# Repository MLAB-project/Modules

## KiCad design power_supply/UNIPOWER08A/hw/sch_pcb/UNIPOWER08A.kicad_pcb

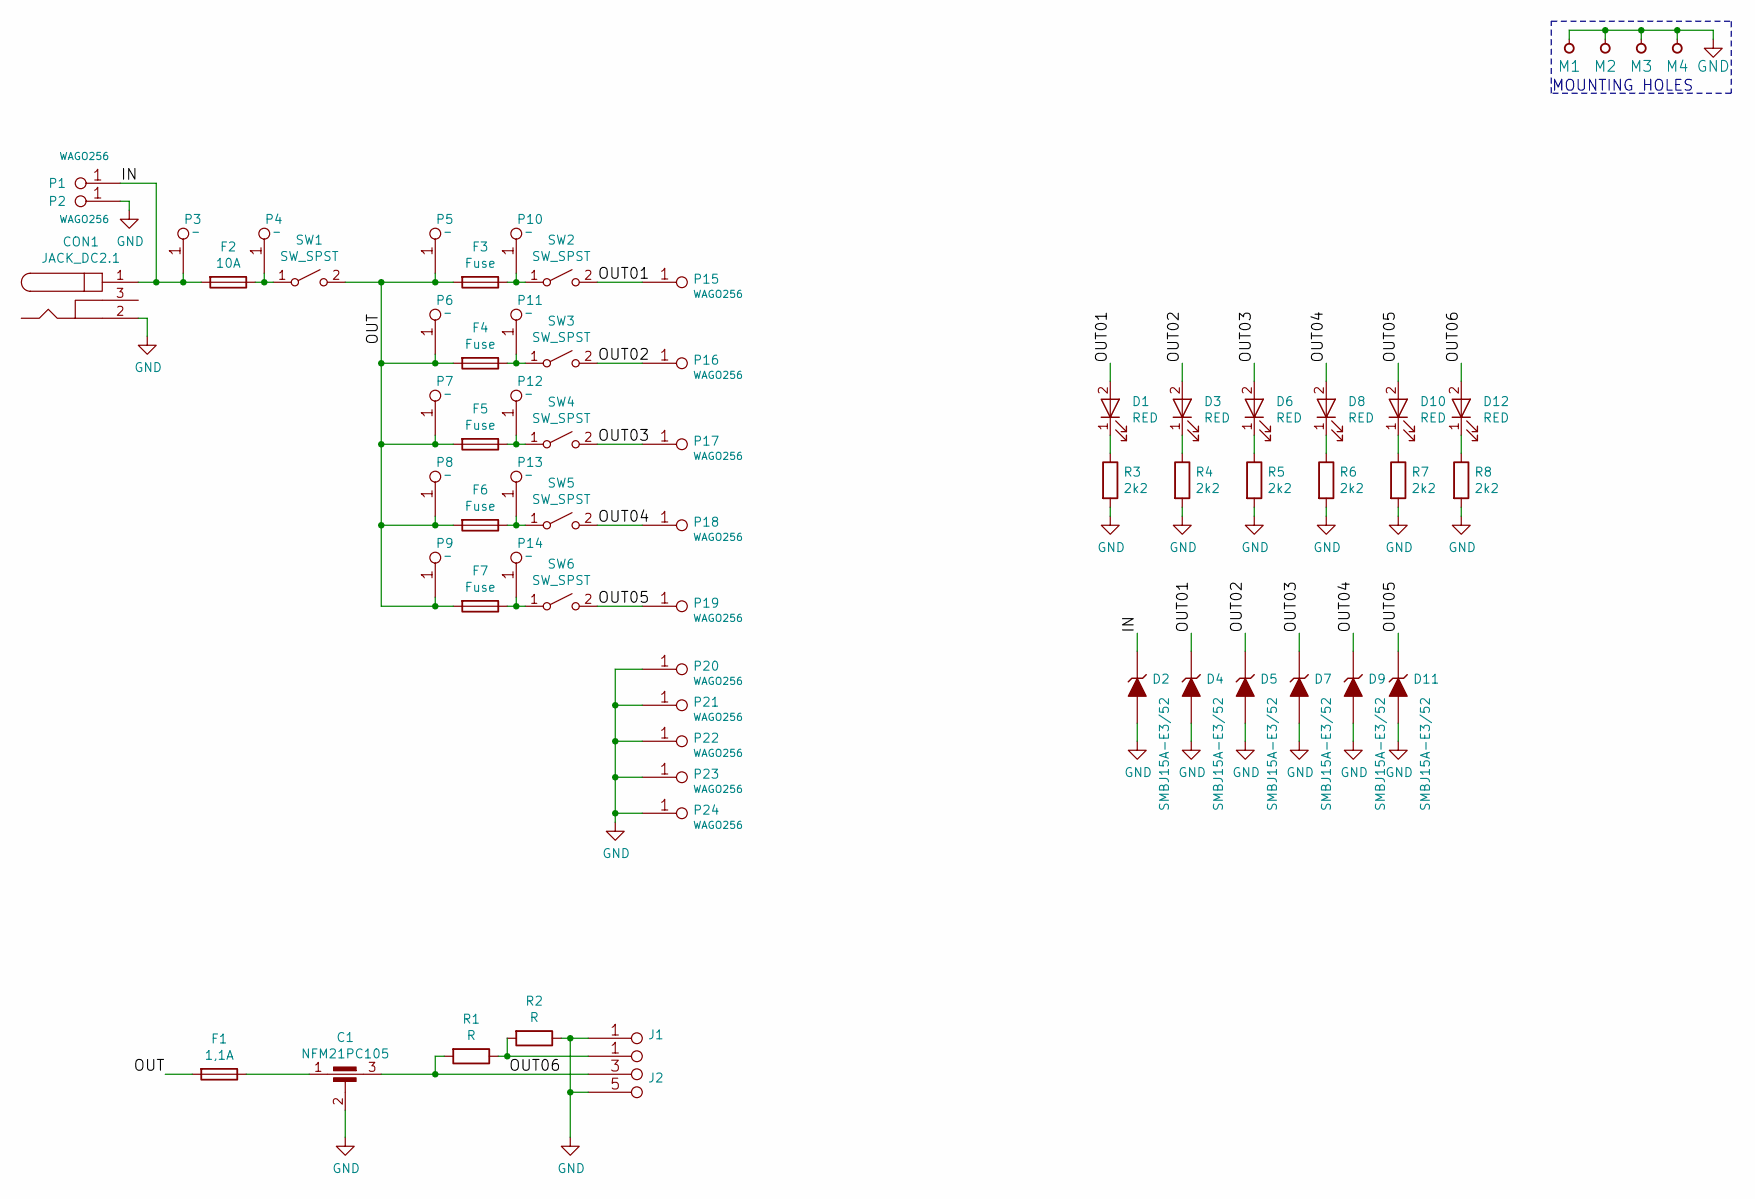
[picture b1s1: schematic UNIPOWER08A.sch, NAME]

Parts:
C1: NFM21PC105; FIR1
CON1: JACK_DC2.1; DC2,1MM
D1, D3, D6, D8, D10, D12: RED; LED_1206
D2, D4, D5, D7, D9, D11: SMBJ15A-E3/52; Diode-SMB_Standard
F1: 1,1A; Drzak_2410
F2: 10A; Drzak_2410
F3, F4, F5, F6, F7: Fuse; Drzak_2410
J1: JUMP_2x1; Straight_2x01
J2: JUMP_3X2; Straight_2x03
M1, M2, M3, M4: HOLE; MountingHole_3mm
P1, P2, P15, P16, P17, P18, P19, P20, P21, P22, P23, P24: WAGO256; WAGO256_2
P3, P4, P5, P6, P7, P8, P9, P10, P11, P12, P13, P14: _; 1_kontakty
R1, R2: R; SMD-0805
R3, R4, R5, R6, R7, R8: 2k2; SMD-0805
SW1, SW2, SW3, SW4, SW5, SW6: SW_SPST; 2_kontakty

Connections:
/IN: CON1.1, D2.1 (K), F2.2, P1.1, P3.1
/OUT: F1.2, F3.2, F4.2, F5.2, F6.2, F7.2, P5.1, P6.1, P7.1, P8.1, P9.1, SW1.2 (B)
/OUT01: D1.2 (A), D4.1 (K), P15.1, SW2.2 (B)
/OUT02: D3.2 (A), D5.1 (K), P16.1, SW3.2 (B)
/OUT03: D6.2 (A), D7.1 (K), P17.1, SW4.2 (B)
/OUT04: D8.2 (A), D9.1 (K), P18.1, SW5.2 (B)
/OUT05: D10.2 (A), D11.1 (K), P19.1, SW6.2 (B)
/OUT06: C1.3, D12.2 (A), J2.3 (4), J2.4, R1.2
GND: C1.2, CON1.2, D2.2 (A), D4.2 (A), D5.2 (A), D7.2 (A), D9.2 (A), D11.2 (A), J1.1, J1.2, J2.5 (6), J2.6, M1.1, M2.1, M3.1, M4.1, P2.1, P20.1, P21.1, P22.1, P23.1, P24.1, R2.1, R3.2, R4.2, R5.2, R6.2, R7.2, R8.2
unnamed: C1.1, F1.1
unnamed: D1.1 (K), R3.1
unnamed: D3.1 (K), R4.1
unnamed: D6.1 (K), R5.1
unnamed: D8.1 (K), R6.1
unnamed: D10.1 (K), R7.1
unnamed: D12.1 (K), R8.1
unnamed: F2.1, P4.1, SW1.1 (A)
unnamed: F3.1, P10.1, SW2.1 (A)
unnamed: F4.1, P11.1, SW3.1 (A)
unnamed: F5.1, P12.1, SW4.1 (A)
unnamed: F6.1, P13.1, SW5.1 (A)
unnamed: F7.1, P14.1, SW6.1 (A)
unnamed: J2.1 (2), J2.2, R1.1, R2.2

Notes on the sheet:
MOUNTING HOLES

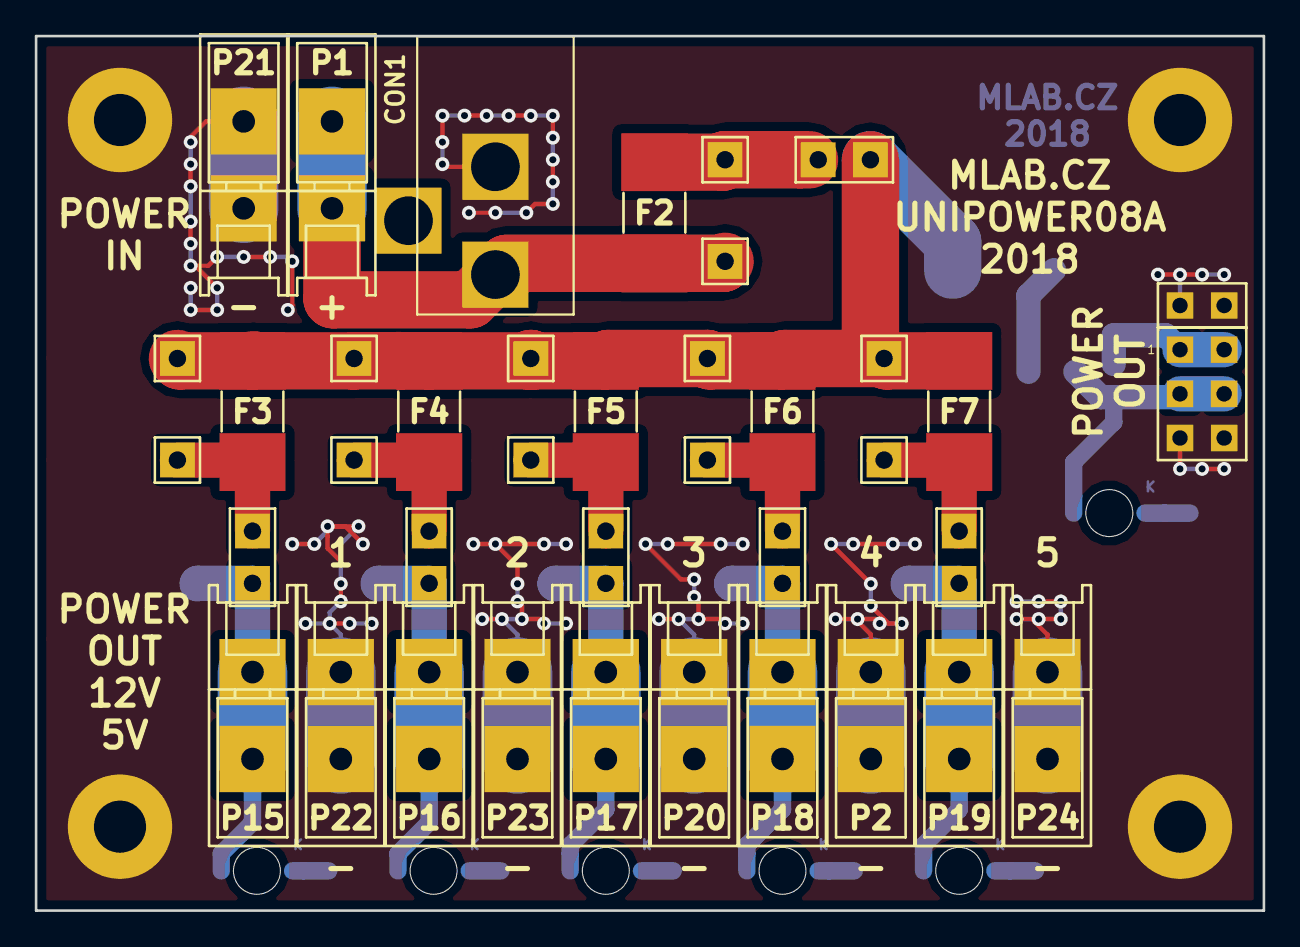
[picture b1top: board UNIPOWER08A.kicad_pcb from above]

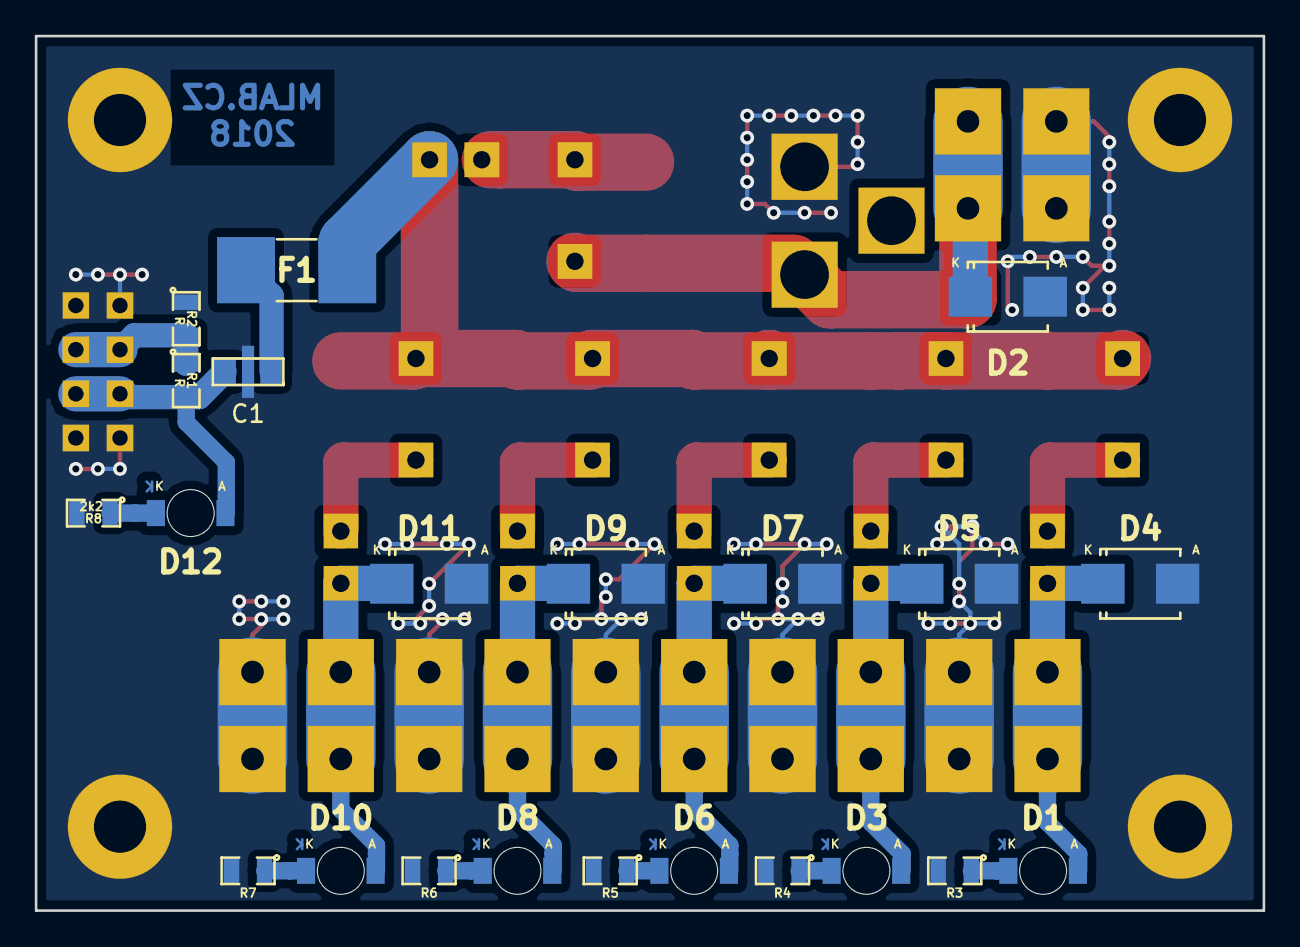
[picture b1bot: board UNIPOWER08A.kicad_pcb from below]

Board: 2 copper layers, 70.6 x 50.3 mm, 65 parts (22 on the bottom side), 23 nets.

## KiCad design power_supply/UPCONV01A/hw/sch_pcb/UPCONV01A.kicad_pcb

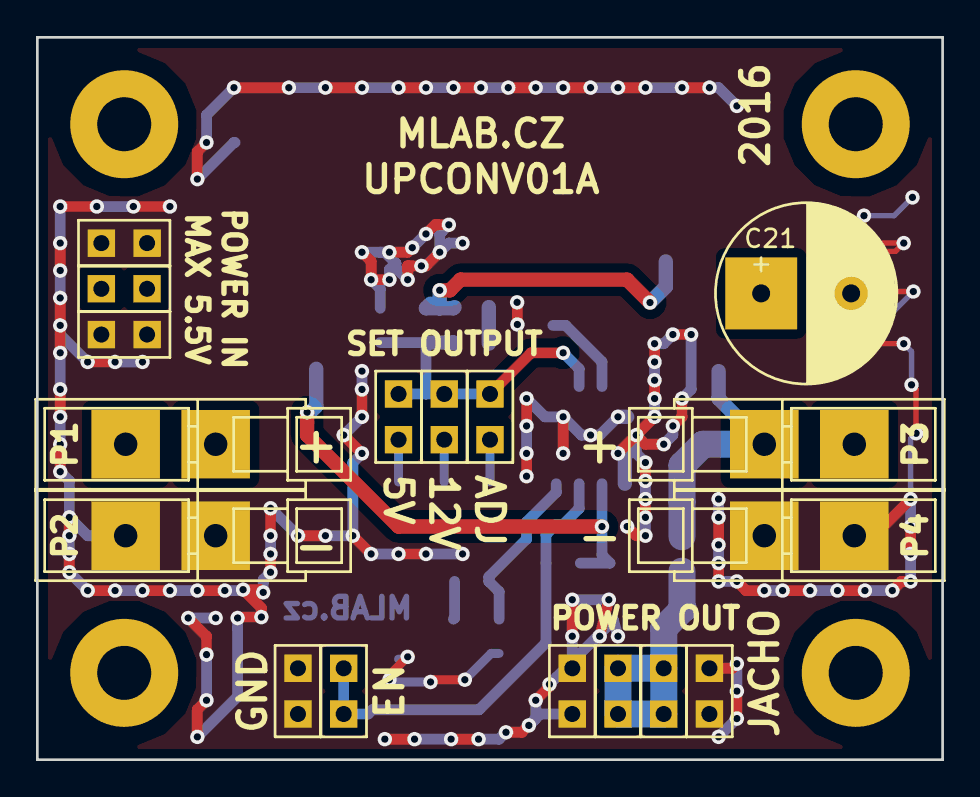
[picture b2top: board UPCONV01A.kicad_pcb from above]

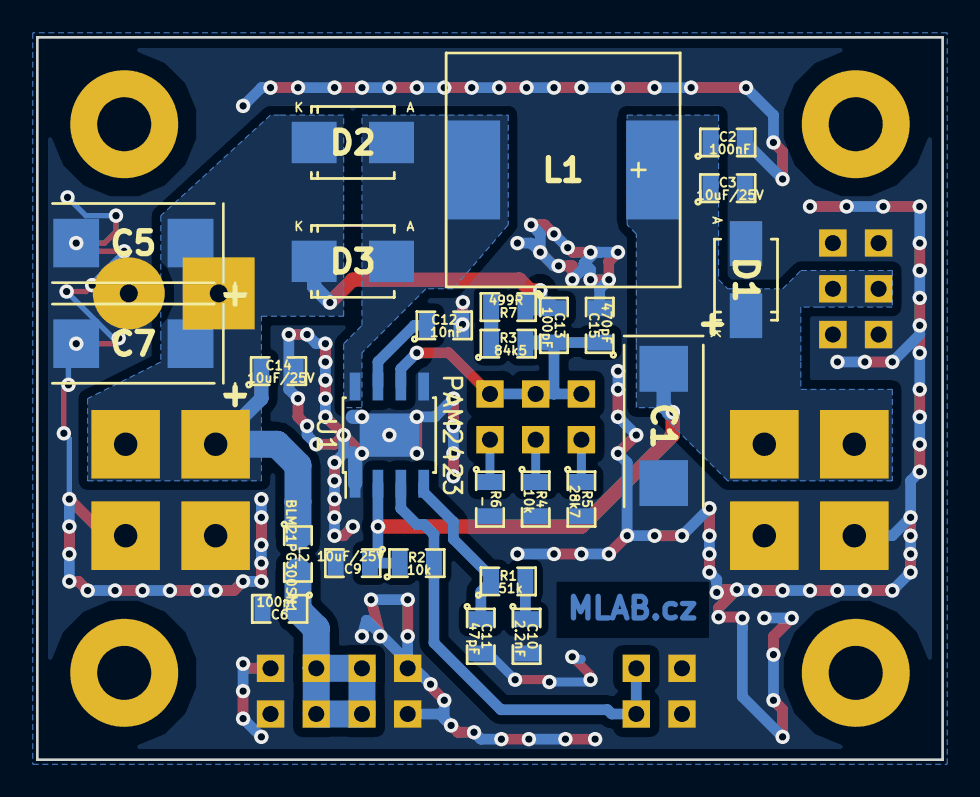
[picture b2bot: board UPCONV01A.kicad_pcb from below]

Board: 2 copper layers, 50.3 x 40.1 mm, 47 parts (26 on the bottom side), 14 nets.

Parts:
C1: 470uF/6V; TantalC_SizeD_Reflow
C2, C6: 100nF; SMD-0805
C3, C9, C14: 10uF/25V; SMD-0805
C5, C7: 220uF; TantalC_SizeD_Reflow
C10: 2.2nF; SMD-0805
C11: 47pF; SMD-0805
C12: 10nF; SMD-0805
C13: 100pF; SMD-0805
C15: 470pF; SMD-0805
C21: 470uF/35V; C_Radial_D10_L13_P5
D1: M4; Diode-SMA_Standard
D2, D3: STPS340U; Diode-SMB_Standard
J1, J2, J3, J7, J8, J9, J10, J11, J12: JUMP_2x1; Straight_1x02
J4, J5, J6: JUMP2_2x1; Straight_1x02
L1: DE1207-10, EPCOS B82477G4682M; DE1205-10
L2: BLM21PG300SN1; SMD-0805
M1, M2, M3, M4: HOLE; MountingHole_3mm
P1, P2, P3, P4: WAGO256
R1: 51k; SMD-0805
R2, R4: 10k; SMD-0805
R3: 84k5; SMD-0805
R5: 28k7; SMD-0805
R6: -; SMD-0805
R7: 499R; SMD-0805
U1: PAM2423; SOP-8_EP_3.9x4.9mm_Pitch1.27mm

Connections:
/5V: J5.1, R5.1
/12V: J4.1, R4.1
/ADJ: J6.1, R6.1
/EN: J2.1, J2.2, R2.2, U1.3
/Vout: C5.1, C7.1, C13.1, C14.1, C21.1, D2.1, D3.1, L2.1, P3.1, R7.1
GND: C1.2, C2.2, C3.2, C5.2, C6.2, C7.2, C9.2, C10.2, C11.2, C12.2, C14.2, C15.2, C21.2, D1.2, J1.1, J1.2, J3.1, J3.2, J7.1, J7.2, J10.1, J10.2, J12.1, J12.2, P2.1, P4.1, R4.2, R5.2, R6.2, U1.1, U1.5, U1.9
unnamed: C6.1, J8.1, J8.2, J9.1, J9.2, L2.2
unnamed: C10.1, R1.2
unnamed: C11.1, R1.1, U1.4
unnamed: C12.1, U1.7
unnamed: C13.2, C15.1, J4.2, J5.2, J6.2, R3.2, U1.6
unnamed: D2.2, D3.2, L1.2, U1.8
unnamed: R3.1, R7.2
VCC: C1.1, C2.1, C3.1, C9.1, D1.1, J11.1, J11.2, L1.1, P1.1, R2.1, U1.2

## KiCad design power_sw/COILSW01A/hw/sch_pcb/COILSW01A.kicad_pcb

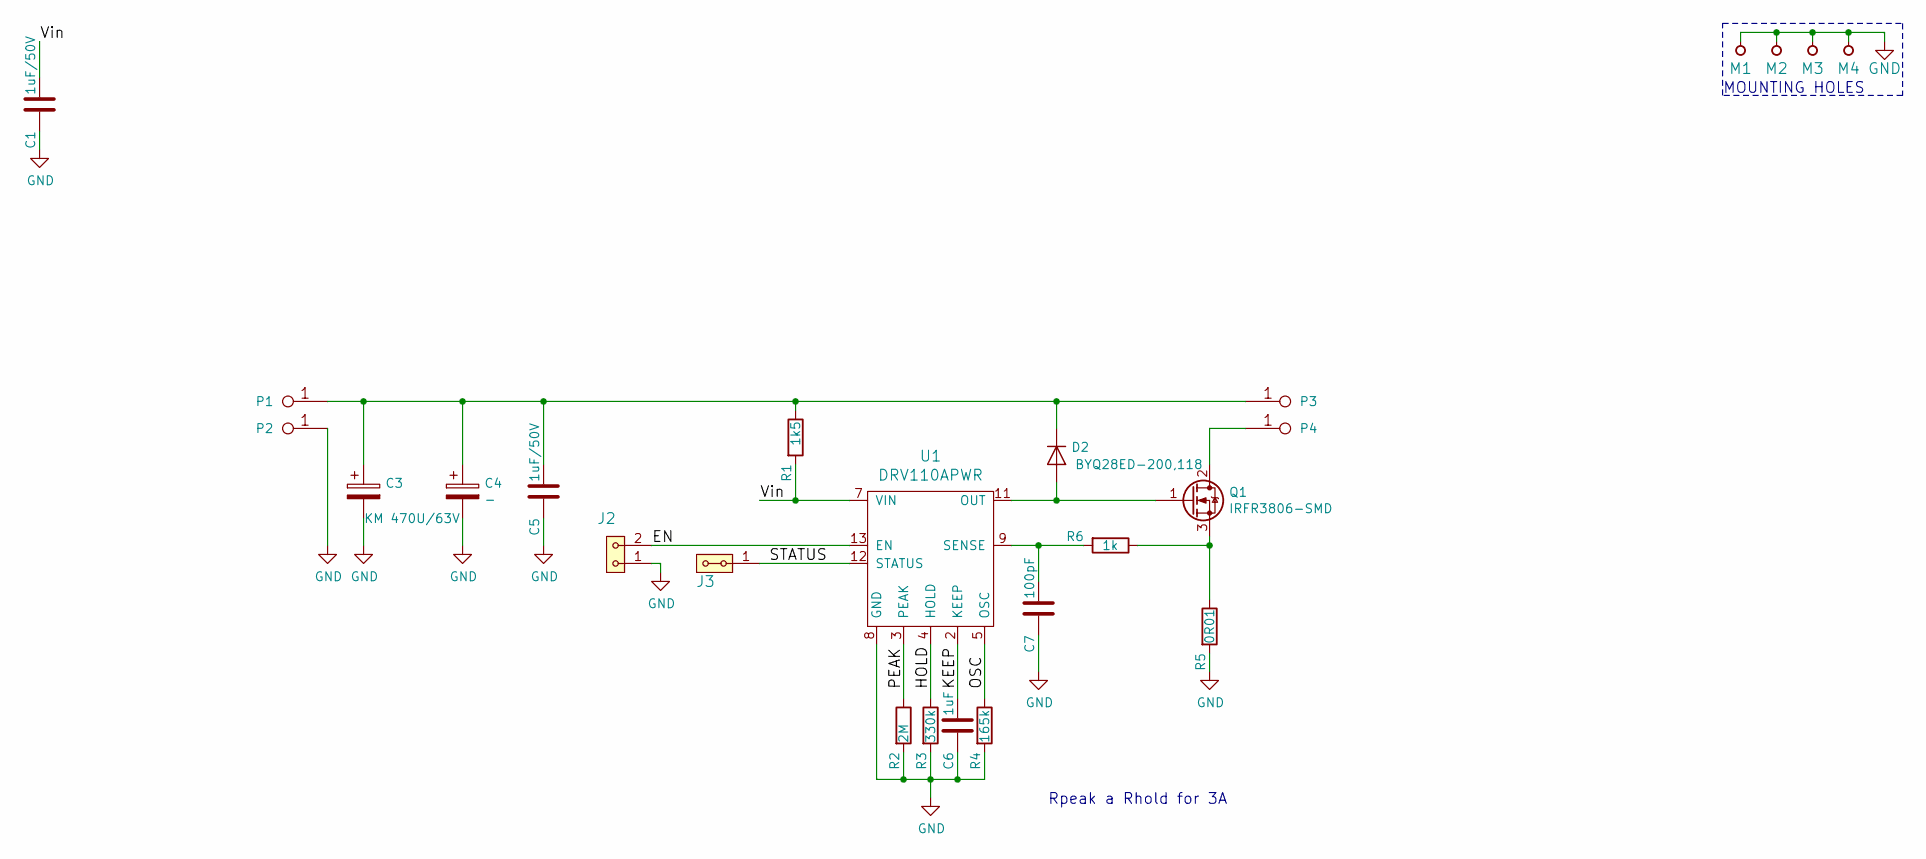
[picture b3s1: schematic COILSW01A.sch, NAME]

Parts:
C1, C5: 1uF/50V; SMD-0805
C3: KM 470U/63V; CP_Radial_D12.5mm_P5.00mm
C4: -; TantalC_SizeD_Reflow
C6: 1uF; SMD-0805
C7: 100pF; SMD-0805
D2: BYQ28ED-200,118; BYQ28ED-200
J2: HEADER_1x02; Straight_1x02
J3: HEADER_2x01_PARALLEL; Straight_1x02
M1, M2, M3, M4: HOLE; MountingHole_3mm
P1, P3, P4: WAGO256-RED; WAGO256
P2: WAGO256-BLUE; WAGO256
Q1: IRFR3806-SMD; TO-252-2
R1: 1k5; SMD-0805
R2: 2M; SMD-0805
R3: 330k; SMD-0805
R4: 165k; SMD-0805
R5: 0R01; SMD-2512
R6: 1k; SMD-0805
U1: DRV110APWR; TSSOP-14_4.4x5mm_P0.65mm

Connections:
/EN: J2.2, U1.13 (EN)
/HOLD: R3.1, U1.4 (HOLD)
/KEEP: C6.1, U1.2 (KEEP)
/OSC: R4.1, U1.5 (OSC)
/PEAK: R2.1, U1.3 (PEAK)
/STATUS: J3.1, J3.2, U1.12 (STATUS)
/Vin: C1.1, R1.2, U1.7 (VIN)
GND: C1.2, C3.2, C4.2, C5.2, C6.2, C7.2, J2.1, M1.1, M2.1, M3.1, M4.1, P2.1, R2.2, R3.2, R4.2, R5.2, U1.8 (GND)
unnamed: C3.1, C4.1, C5.1, D2.1 (K), P1.1, P3.1, R1.1
unnamed: C7.1, R6.2, U1.9 (SENSE)
unnamed: D2.2 (A), Q1.1 (G), U1.11 (OUT)
unnamed: P4.1, Q1.2 (D)
unnamed: Q1.3 (S), R5.1, R6.1

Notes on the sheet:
MOUNTING HOLES
Rpeak a Rhold for 3A

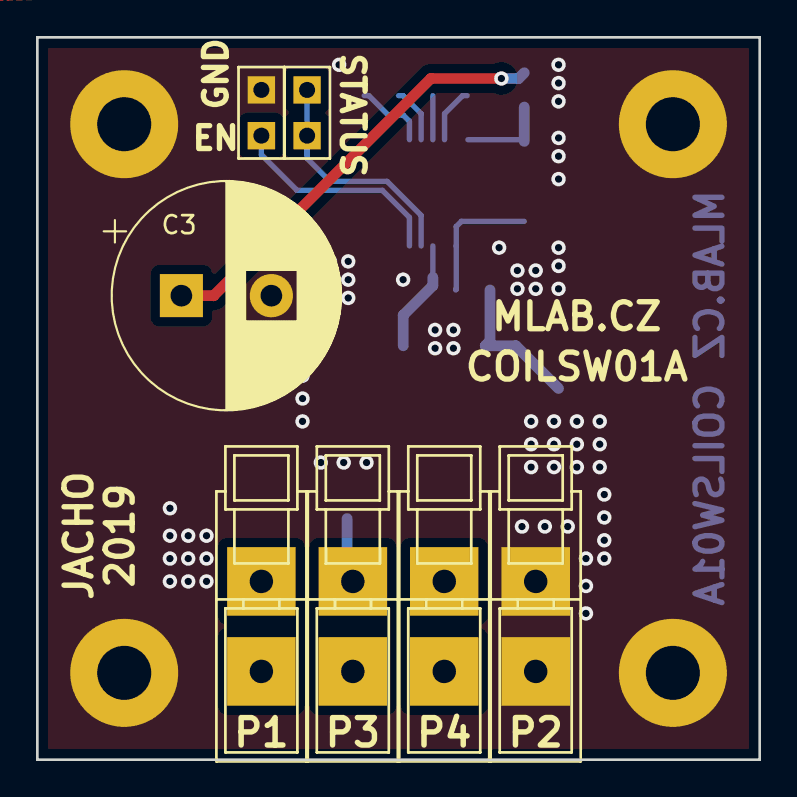
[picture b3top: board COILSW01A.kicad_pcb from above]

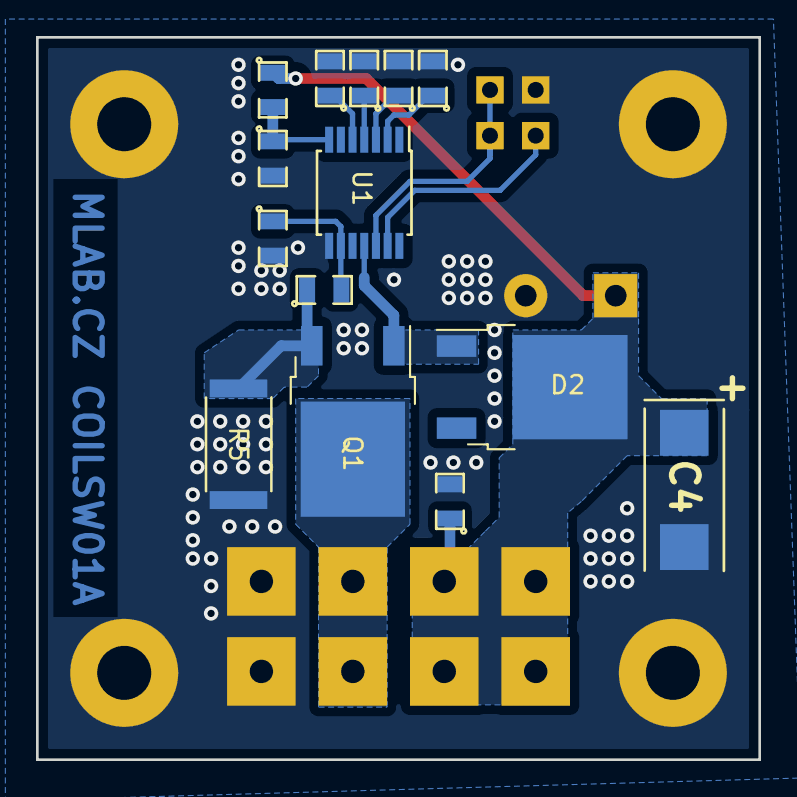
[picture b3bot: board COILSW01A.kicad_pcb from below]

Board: 2 copper layers, 40.1 x 40.1 mm, 25 parts (14 on the bottom side), 13 nets.

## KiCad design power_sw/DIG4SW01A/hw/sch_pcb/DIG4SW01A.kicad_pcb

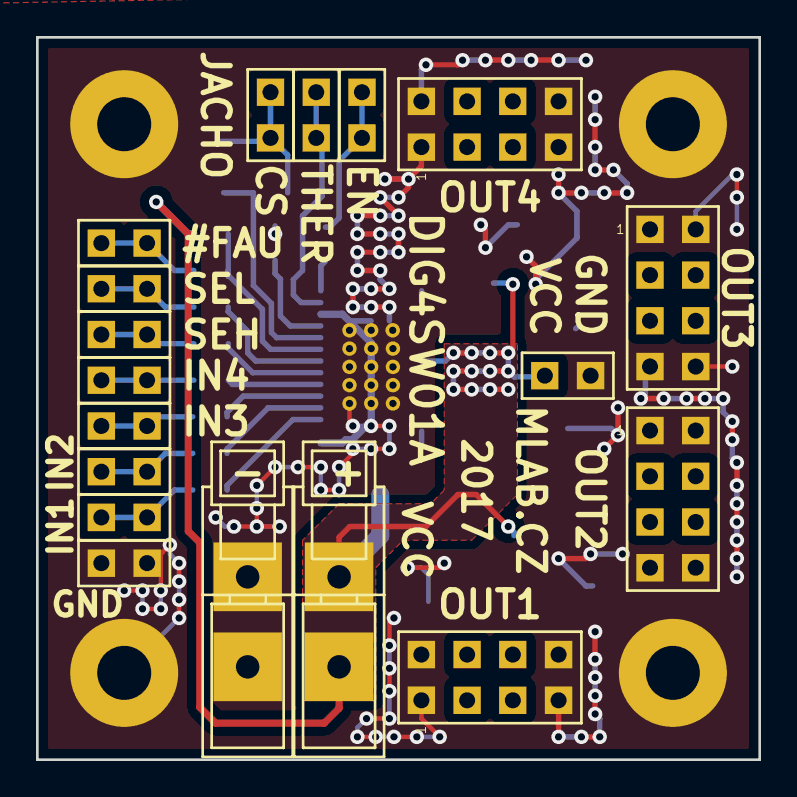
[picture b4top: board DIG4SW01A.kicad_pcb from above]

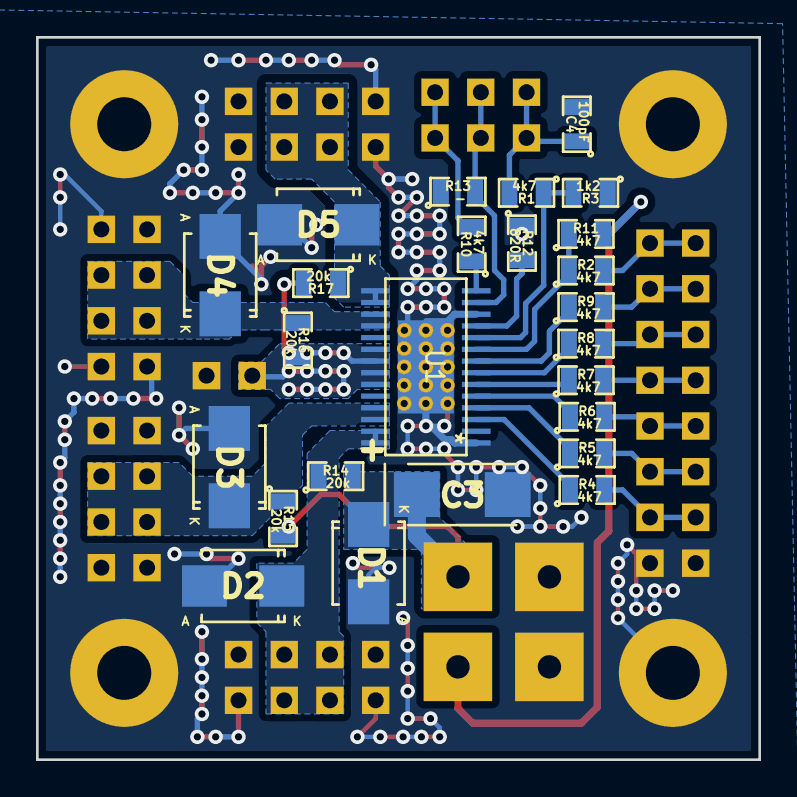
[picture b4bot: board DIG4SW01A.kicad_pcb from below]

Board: 2 copper layers, 40.1 x 40.1 mm, 47 parts (25 on the bottom side), 26 nets.

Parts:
C3: 47uF/16V; TantalC_SizeC_Reflow
C4: 100pF; SMD-0805
D1: STPS340U; Diode-SMB_Standard
D2, D3, D4, D5: SMBJ15A-E3/52; SMB_Standard
J1, J2: CONN1_1; WAGO256
J3: CONN1_2; Straight_1x02
J4, J5, J6, J7, J8, J9, J10, J11, J12, J13, J18: JUMP_2x1; Straight_2x01
J14, J15, J16, J17: JUMP_4X2; Straight_2x04
M1, M2, M3, M4: HOLE; MountingHole_3mm
R1, R2, R4, R5, R6, R7, R8, R9, R10, R11: 4k7; SMD-0805
R3: 1k2; SMD-0805
R12: 820R; SMD-0805
R13: -; SMD-0805
R14, R15, R16, R17: 20k; SMD-0805
U1: TPS4H160-Q1-B; HTSSOP28

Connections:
/#FAULT: J4.1, J4.2, R2.2
/CS: C4.1, J5.1, J5.2, R1.2
/DIAG_EN: J12.1, J12.2, R10.2
/IN1: J6.1, J6.2, R4.2
/IN2: J7.1, J7.2, R5.2
/IN3: J8.1, J8.2, R6.2
/IN4: J9.1, J9.2, R7.2
/OUT1: D2.1, J14.3, J14.4, J14.5, J14.6, R14.1, U1.27, U1.28
/OUT2: D3.1, J15.3, J15.4, J15.5, J15.6, R15.1, U1.25, U1.26
/OUT3: D4.1, J16.3, J16.4, J16.5, J16.6, R16.1, U1.17, U1.18
/OUT4: D5.1, J17.3, J17.4, J17.5, J17.6, R17.1, U1.15, U1.16
/SEH: J10.1, J10.2, R8.2
/SEL: J11.1, J11.2, R9.2
/THER: J13.1, J13.2, R13.2, U1.13
GND: C3.2, C4.2, D1.2, D2.2, D3.2, D4.2, D5.2, J2.1, J3.2, J14.1, J14.2, J14.7, J14.8, J15.1, J15.2, J15.7, J15.8, J16.1, J16.2, J16.7, J16.8, J17.1, J17.2, J17.7, J17.8, J18.1, J18.2, M1.1, M2.1, M3.1, M4.1, R3.1, R12.1, R13.1, U1.1, U1.12, U1.29
unnamed: R1.1, R3.2, U1.10
unnamed: R4.1, U1.3
unnamed: R5.1, U1.4
unnamed: R6.1, U1.5
unnamed: R7.1, U1.6
unnamed: R8.1, U1.7
unnamed: R9.1, U1.8
unnamed: R10.1, U1.14
unnamed: R2.1, R11.1, U1.9
unnamed: R12.2, U1.11
VCC: C3.1, D1.1, J1.1, J3.1, R11.2, R14.2, R15.2, R16.2, R17.2, U1.20, U1.21, U1.22, U1.23

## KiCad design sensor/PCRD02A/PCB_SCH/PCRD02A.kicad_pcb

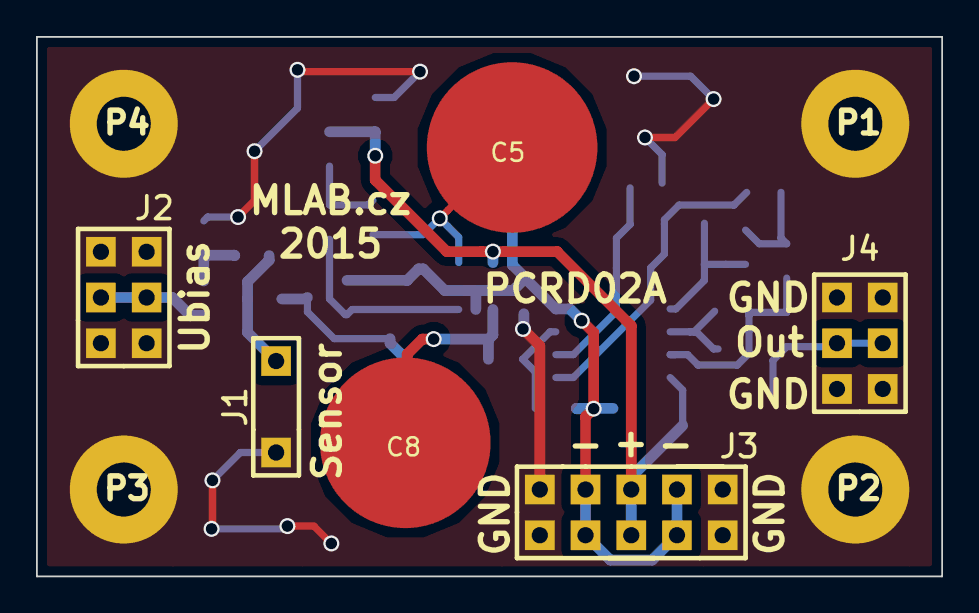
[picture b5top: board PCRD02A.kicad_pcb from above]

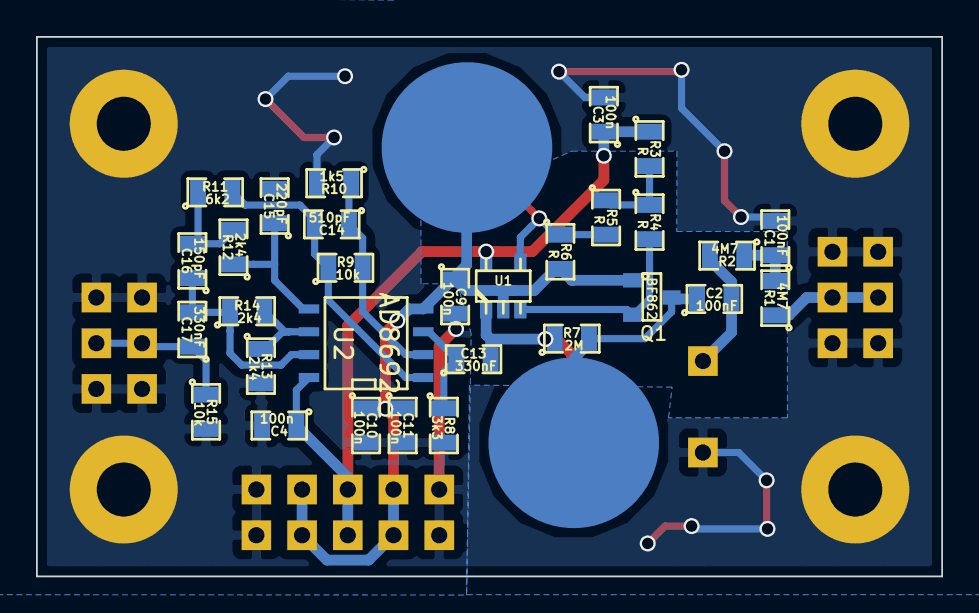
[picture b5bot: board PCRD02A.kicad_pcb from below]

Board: 2 copper layers, 50.3 x 30.0 mm, 40 parts (30 on the bottom side), 19 nets.

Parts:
C1, C2: 100nF; SMD-0805
C3, C4, C9, C10, C11: 100n; SMD-0805
C5, C8: 2pF; 2pF_PCB
C13, C17: 330nF; SMD-0805
C14: 510pF; SMD-0805
C15: 220pF; SMD-0805
C16: 150pF; SMD-0805
J1: CONN1_2; CONN_3_2
J2: JUMP_3X2; Pin_Header_Straight_2x03
J3: JUMP_5X2; Pin_Header_Straight_2x05
J4: Out; Pin_Header_Straight_2x03
P1, P2, P3, P4: _; MountingHole_3mm
Q1: BF862; SOT-23
R1, R2: 4M7; SMD-0805
R3, R4, R5, R6: R; SMD-0805
R7: 2M; SMD-0805
R8: 3k3; SMD-0805
R9, R15: 10k; SMD-0805
R10: 1k5; SMD-0805
R11: 6k2; SMD-0805
R12, R13, R14: 2k4; SMD-0805
U1: AD8691; tsot-5
U2: AD8692; SOIC-8-N

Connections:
GND: C1.2, C3.2, C4.2, C9.2, C10.2, C11.2, C15.2, J1.1, J2.1, J2.3, J2.4, J2.6, J3.1, J3.5, J3.6, J3.10, J4.1, J4.3, J4.4, J4.6, P1.1, P2.1, P3.1, P4.1, R8.2, R10.2, R13.2, R15.2
unnamed: C1.1, R1.2, R2.1
unnamed: C2.1, C8.2, Q1.3, R7.2
unnamed: C2.2, J1.2, R2.2
unnamed: C5.1, R5.2, R6.1, U1.4
unnamed: C13.1, R8.1, U2.3
unnamed: C8.1, C13.2, R7.1, U1.1
unnamed: C14.1, R9.2, R10.1, U2.2
unnamed: C14.2, R9.1, R11.2, U2.1
unnamed: C15.1, R12.1, U2.5
unnamed: C16.1, C17.2, R14.1, U2.7
unnamed: C16.2, R11.1, R12.2
unnamed: C17.1, J4.2, J4.5, R15.1
unnamed: J2.2, J2.5, R1.1
unnamed: Q1.2, R4.2, U1.3
unnamed: R3.2, R4.1, R5.1
unnamed: R13.1, R14.2, U2.6
V+: C3.1, C4.1, J3.3, J3.8, R3.1, U1.5, U2.8
V-: C5.2, C9.1, C10.1, C11.1, J3.2, J3.4, J3.7, J3.9, Q1.1, R6.2, U1.2, U2.4

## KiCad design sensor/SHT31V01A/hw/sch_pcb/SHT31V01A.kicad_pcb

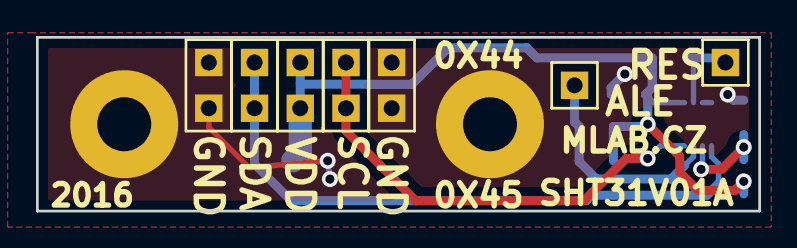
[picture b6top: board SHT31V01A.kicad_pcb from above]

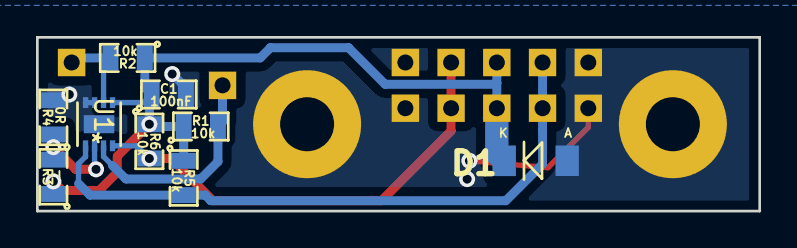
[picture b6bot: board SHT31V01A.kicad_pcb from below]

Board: 2 copper layers, 40.1 x 9.7 mm, 18 parts (9 on the bottom side), 7 nets.

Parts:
C1: 100nF; SMD-0805
D1: BZV55C-5,6V; Diode-MiniMELF_Standard
J1, J2: CONN1_1; Straight_1x01
J9, J10, J11, J12, J13: JUMP_2x1; Straight_1x02
M1, M2: HOLE; MountingHole_3mm
R1, R2, R5, R6: 10k; SMD-0805
R3: -; SMD-0805
R4: 0R; SMD-0805
U1: SHT31; DFN-8-1EP_2.4x2.4mm_Pitch0.5mm

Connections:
+3V3: C1.1, D1.2, J9.1, J9.2, R1.1, R2.1, R3.1, R5.1, R6.1, U1.5
/ALERT: J1.1, R1.2, U1.3
/SCL: J11.1, J11.2, R6.2, U1.4
/SDA: J10.1, J10.2, R5.2, U1.1
/nRESET: J2.1, R2.2, U1.6
GND: C1.2, D1.1, J12.1, J12.2, J13.1, J13.2, M1.1, M2.1, R4.2, U1.7, U1.8, U1.9
unnamed: R3.2, R4.1, U1.2

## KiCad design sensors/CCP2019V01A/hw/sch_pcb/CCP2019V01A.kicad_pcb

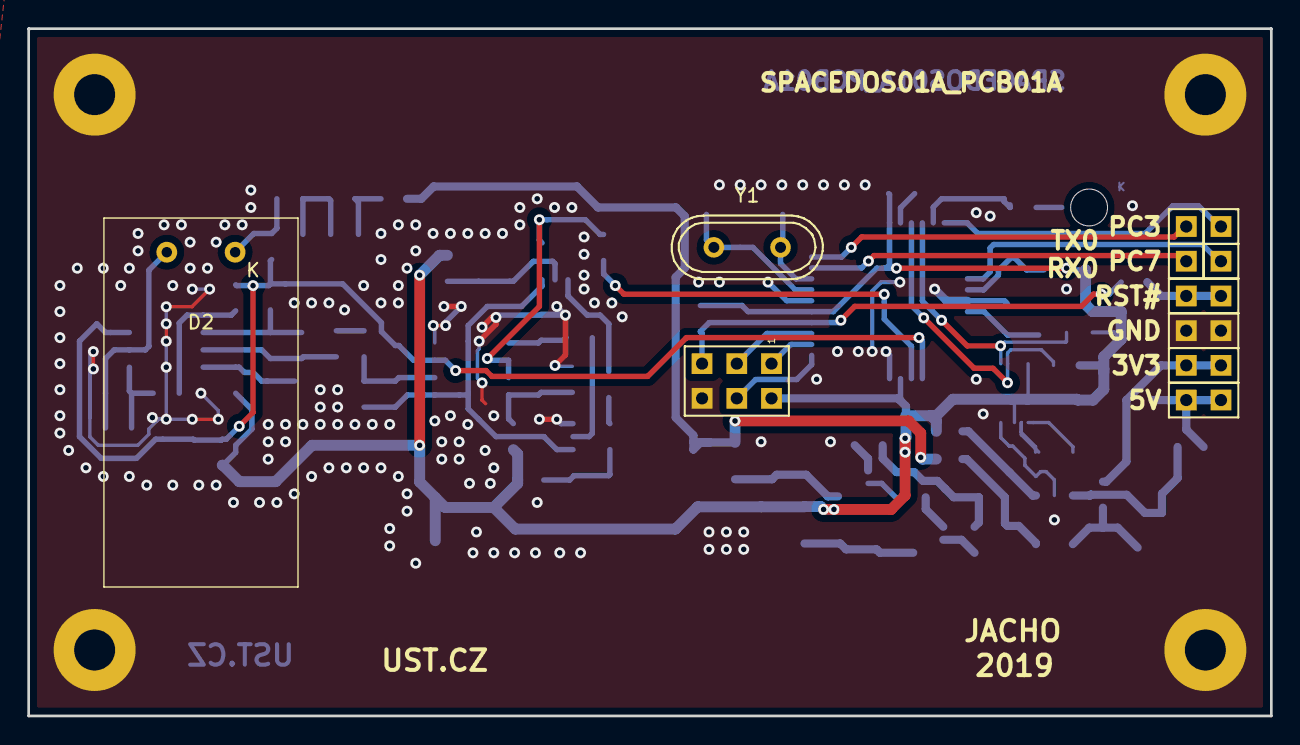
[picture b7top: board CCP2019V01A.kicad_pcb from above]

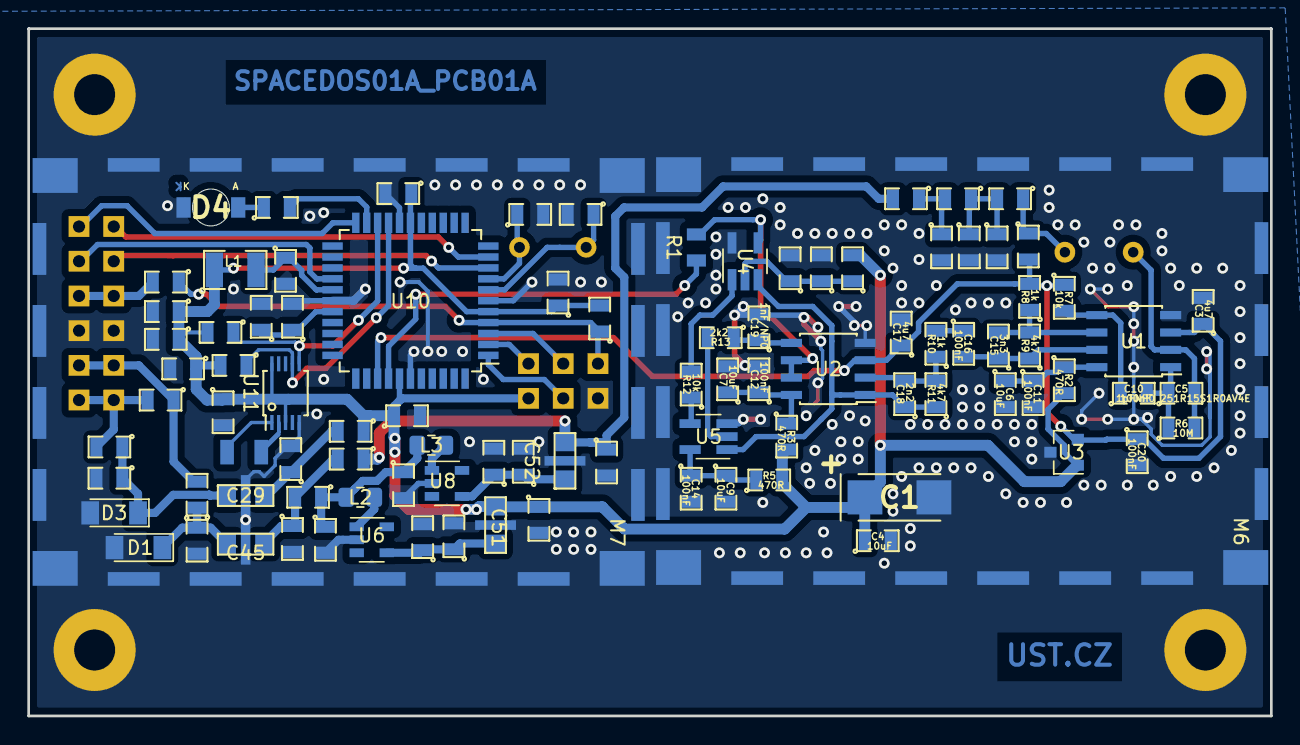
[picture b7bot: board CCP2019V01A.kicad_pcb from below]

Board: 2 copper layers, 90.9 x 50.3 mm, 111 parts (96 on the bottom side), 55 nets.

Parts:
C1: 47uF; TantalC_SizeC_Reflow
C2, C10, C11, C12, C13, C14, C16, C20, C25, C26, C27, C28, C31, C32, C34, C35, C39, C44, C47, C48, C53, C54, C55: 100nF; SMD-0805
C3, C17, C43: 4u7; SMD-0805
C4, C6, C7, C8, C9, C21, C22, C23, C36, C38, C40, C42, C49, C50: 10uF; SMD-0805
C5: 1pFNP0 251R15S1R0AV4E; SMD-0805
C15: 3n3; SMD-0805
C18: 2n2; SMD-0805
C19: 1nF/NP0; SMD-0805
C24: 1uF; SMD-0805
C29, C45, C51, C52: NFM21PC105-1uF; FIR1
C30, C33: 15pF; SMD-0805
D1, D3: BZV55C-5,6V; D_MiniMELF
D2: S2744-09; HAMAMATSU_S2744-09
D4: HLMP-K150+FIX-LED-313; LED_1206
F1, F2: SR010-15 100mA; SMD-0805
J1, J2, J3: HEADER_2x01_PARALLEL; Straight_1x02
J4, J5, J6, J7: HEADER_1x01; Straight_1x01
J19: HEADER_2x01_PARALLEL; Straight_2x01
J22: HEADER_2x03; Straight_2x03
L1: 10uH - LQH32CN100K23L; SMD-1210
L2, L3: DFE252012P-4R7M; R_0805_2012Metric_Pad1.15x1.40mm_HandSolder
M1, M2, M3, M4: HOLE; MountingHole_3mm
M6, M7: BMI-S-210-F
R1: 10R; SMD-0805
R2, R3, R4, R5: 470R; SMD-0805
R6: 10M; SMD-0805
R7, R12, R20, R21, R23: 10k; SMD-0805
R8, R10: 1k; SMD-0805
R9, R11, R15, R19, R22: 4k7; SMD-0805
R13, R26: 2k2; SMD-0805
R24, R25, R27: -; SMD-0805
R28: 0R; SMD-0805
U1, U2: OPA2314; SOIC-8_3.9x4.9mm_Pitch1.27mm
U3: ISL21080DIH312Z-TK 1V25; SOT-23
U4: TS7211; SOT-23-5_HandSoldering
U5: TS5A4594; SOT-23-5_HandSoldering
U6: TPS613221ADBV; SOT-23-5
U8: TPS613222ADBV; SOT-23-5
U10: ATMEGA1284P-AU; TQFP-44_10x10mm_P0.8mm
U11: PCF85263A; TSSOP-10_3x3mm_Pitch0.5mm
Y1: 16MHz; Crystal_HC49-U_Vertical
Y2: ABS07-120-32.768KHZ-T; ABS07

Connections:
+3V3: C1.1, C4.1, C26.1, C27.1, C28.1, C34.1, C35.1, C39.1, C47.1, C51.3, C53.1, J22.2, L1.1, R2.2, R3.2, R4.2, R5.2, R20.2, R21.2, R23.2, R27.1, U3.1, U10.5, U10.17, U10.38, U11.3, U11.10
+5V: C52.3, C54.1, R15.2, R25.1
/A: C5.2, D2.2, R6.2, U1.2
/K: C24.1, D2.1, R22.1
/VCC1: C6.1, C11.1, R2.1, U1.8
/VCC2: C7.1, C12.1, R3.1, U2.8
/VCC3: C8.1, C13.1, R4.1, U4.2
/VCC4: C9.1, C14.1, R5.1, U5.5
/cpu/AVCC: C31.1, L1.2, U10.27
/cpu/LED: R26.2, U10.21
/cpu/PB5: J22.4, U10.1
/cpu/PB6: J22.1, U10.2
/cpu/PB7: J22.3, U10.3
/cpu/PC0: R21.1, U10.19, U11.7
/cpu/PC1: R20.1, U10.20, U11.6
/cpu/PC3: J5.1, U10.22
/cpu/PC7: J4.1, U10.26
/cpu/RST#: C43.2, J19.1, J19.2
/cpu/RST#_P: C43.1, J22.5, R23.1, U10.4
/cpu/RX0: J6.1, U10.9
/cpu/TX0: J7.1, U10.10
/power/3: F2.2, J3.1, J3.2, R24.2
/power/5: F1.2, J1.1, J1.2, R24.1
GND: C1.2, C2.2, C3.2, C4.2, C6.2, C7.2, C8.2, C9.2, C11.2, C12.2, C13.2, C14.2, C17.2, C19.2, C20.2, C21.2, C22.2, C23.2, C25.2, C26.2, C27.2, C28.2, C29.2, C30.2, C31.2, C32.2, C33.2, C34.2, C35.2, C36.2, C38.2, C39.2, C40.2, C42.2, C44.2, C45.2, C47.2, C48.2, C49.2, C50.2, C51.2, C52.2, C53.2, C54.2, C55.2, D1.2, D3.2, D4.1, J2.1, J2.2, J22.6, M1.1, M2.1, M3.1, M4.1, M6.1, M7.1, U1.4, U2.4, U3.3, U4.5, U5.3, U6.2, U8.2, U10.6, U10.18, U10.28, U10.39, U11.5
unnamed: C2.1, C23.1, R19.1, R22.2
unnamed: C10.1, R7.2, U1.5
unnamed: C5.1, C10.2, R6.1, U1.1
unnamed: C15.1, C16.2, R9.1, U1.7
unnamed: C15.2, R8.1, R9.2, U1.6
unnamed: C16.1, R10.2
unnamed: C18.1, R11.1, U2.1, U4.3, U5.1
unnamed: C18.2, R10.1, R11.2, U2.2
unnamed: C19.1, R13.1, U2.5
unnamed: C21.1, R15.1, R19.2
unnamed: C22.1, C45.1, D1.1, F1.1
unnamed: C29.1, C36.1, D3.1, F2.1
unnamed: C29.3, C55.1, R27.2
unnamed: C30.1, U10.7, Y1.1
unnamed: C33.1, U10.8, Y1.2
unnamed: C38.1, C49.1, C51.1, U6.4
unnamed: C40.1, C44.1, U10.29
unnamed: C42.1, C50.1, C52.1, U8.4
unnamed: C45.3, C48.1, R25.2, R28.2
unnamed: D4.2, R26.1
unnamed: L2.2, U6.1
unnamed: L3.2, U8.1
unnamed: R1.2, U2.6, U2.7, U4.4
unnamed: R12.1, U5.4
unnamed: R12.2, U4.1
unnamed: R13.2, U5.2
unnamed: U11.1, Y2.2
unnamed: U11.2, Y2.1
PA0: R1.1, U10.37
PA1: C3.1, C17.1, C20.1, C24.2, R7.1, R8.2, U1.3, U2.3, U3.2, U10.36
VDD: C25.1, C32.1, L2.1, L3.1, R28.1
